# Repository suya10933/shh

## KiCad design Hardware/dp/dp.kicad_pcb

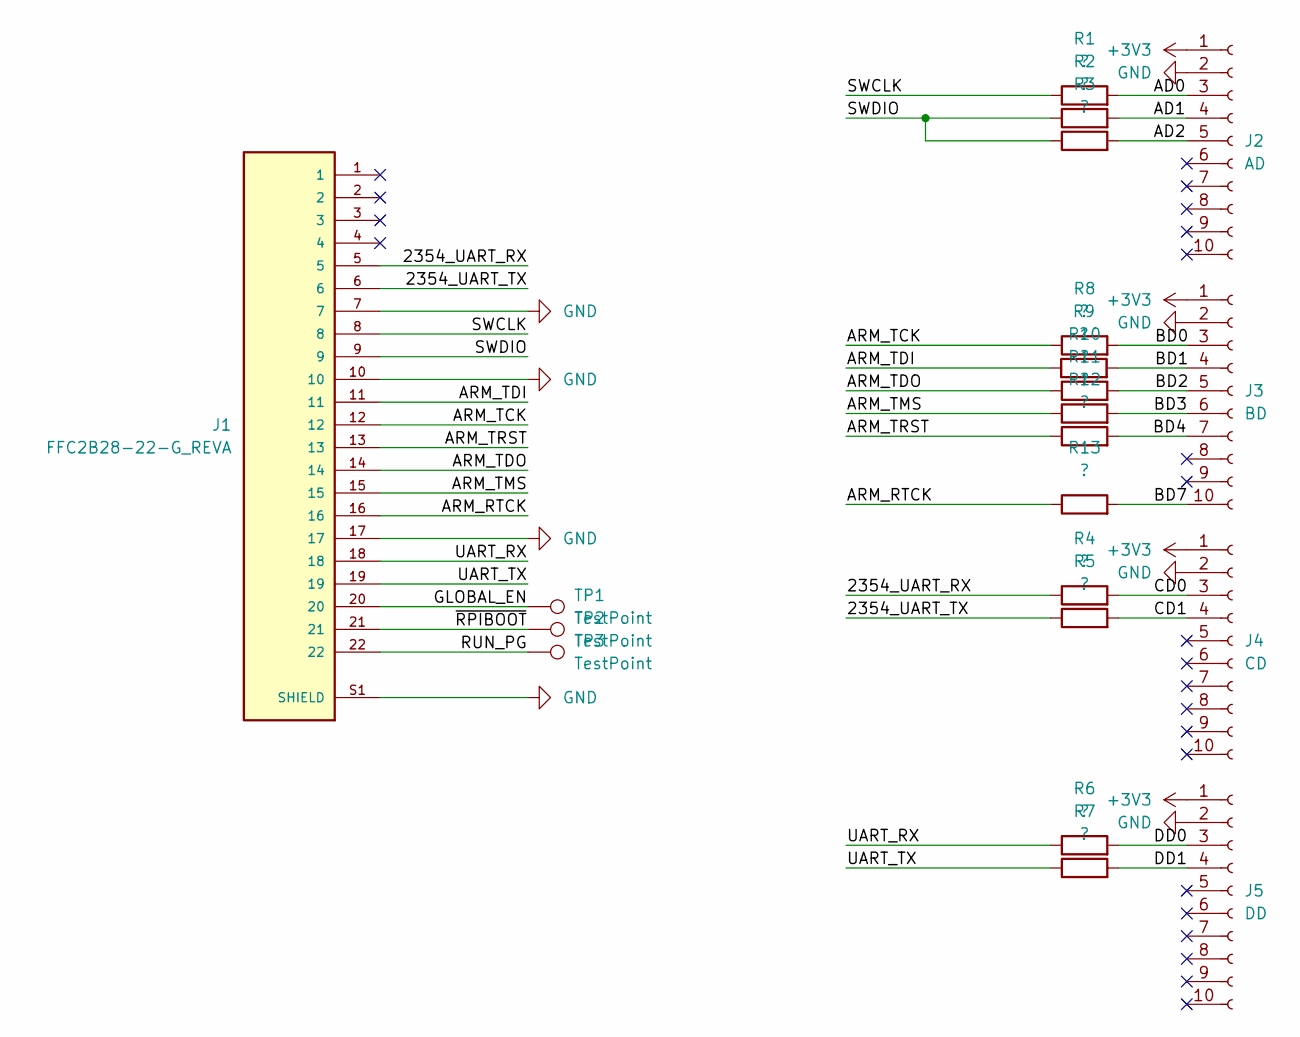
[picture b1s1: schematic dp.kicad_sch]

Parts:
J1: FFC2B28-22-G_REVA; GCT_FFC2B28-22-G_REVA; PARTREV A
J2: AD; PinSocket_1x10_P2.54mm_Vertical
J3: BD; PinSocket_1x10_P2.54mm_Vertical
J4: CD; PinSocket_1x10_P2.54mm_Vertical
J5: DD; PinSocket_1x10_P2.54mm_Vertical
R1, R2, R3, R4, R5, R6, R7, R8, R9, R10, R11, R12, R13: ?; R_0805_2012Metric_Pad1.20x1.40mm_HandSolder
TP1, TP2, TP3: TestPoint; TestPoint_Pad_1.0x1.0mm

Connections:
+3V3: J2.1, J3.1, J4.1, J5.1
/2354_UART_RX: J1.5, R4.1
/2354_UART_TX: J1.6, R5.1
/AD0: J2.3, R1.2
/AD1: J2.4, R2.2
/AD2: J2.5, R3.2
/ARM_RTCK: J1.16, R13.1
/ARM_TCK: J1.12, R8.1
/ARM_TDI: J1.11, R9.1
/ARM_TDO: J1.14, R10.1
/ARM_TMS: J1.15, R11.1
/ARM_TRST: J1.13, R12.1
/BD0: J3.3, R8.2
/BD1: J3.4, R9.2
/BD2: J3.5, R10.2
/BD3: J3.6, R11.2
/BD4: J3.7, R12.2
/BD7: J3.10, R13.2
/CD0: J4.3, R4.2
/CD1: J4.4, R5.2
/DD0: J5.3, R6.2
/DD1: J5.4, R7.2
/GLOBAL_EN: J1.20, TP1.1 (1_1)
/RUN_PG: J1.22, TP3.1 (1_1)
/SWCLK: J1.8, R1.1
/SWDIO: J1.9, R2.1, R3.1
/UART_RX: J1.18, R6.1
/UART_TX: J1.19, R7.1
/~RPIBOOT: J1.21, TP2.1 (1_1)
GND: J1.7, J1.10, J1.17, J1.S1 (SHIELD), J1.S2 (SHIELD), J2.2, J3.2, J4.2, J5.2

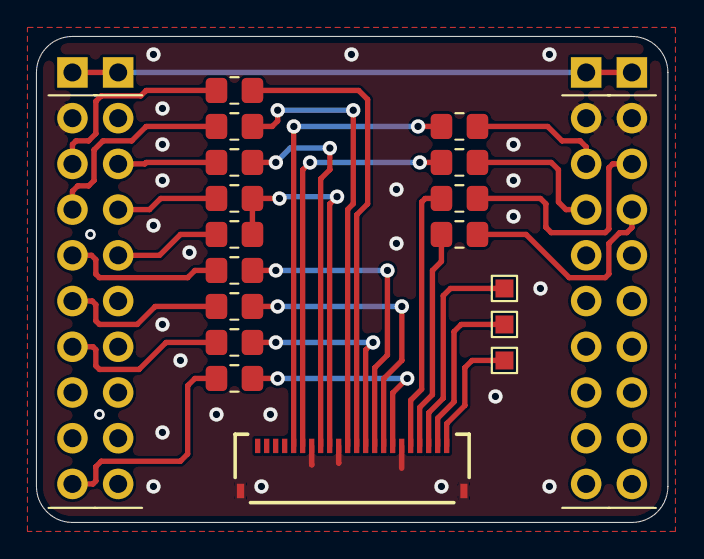
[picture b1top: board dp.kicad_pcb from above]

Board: 2 copper layers, 35.1 x 27.0 mm, 21 parts (0 on the bottom side), 30 nets.

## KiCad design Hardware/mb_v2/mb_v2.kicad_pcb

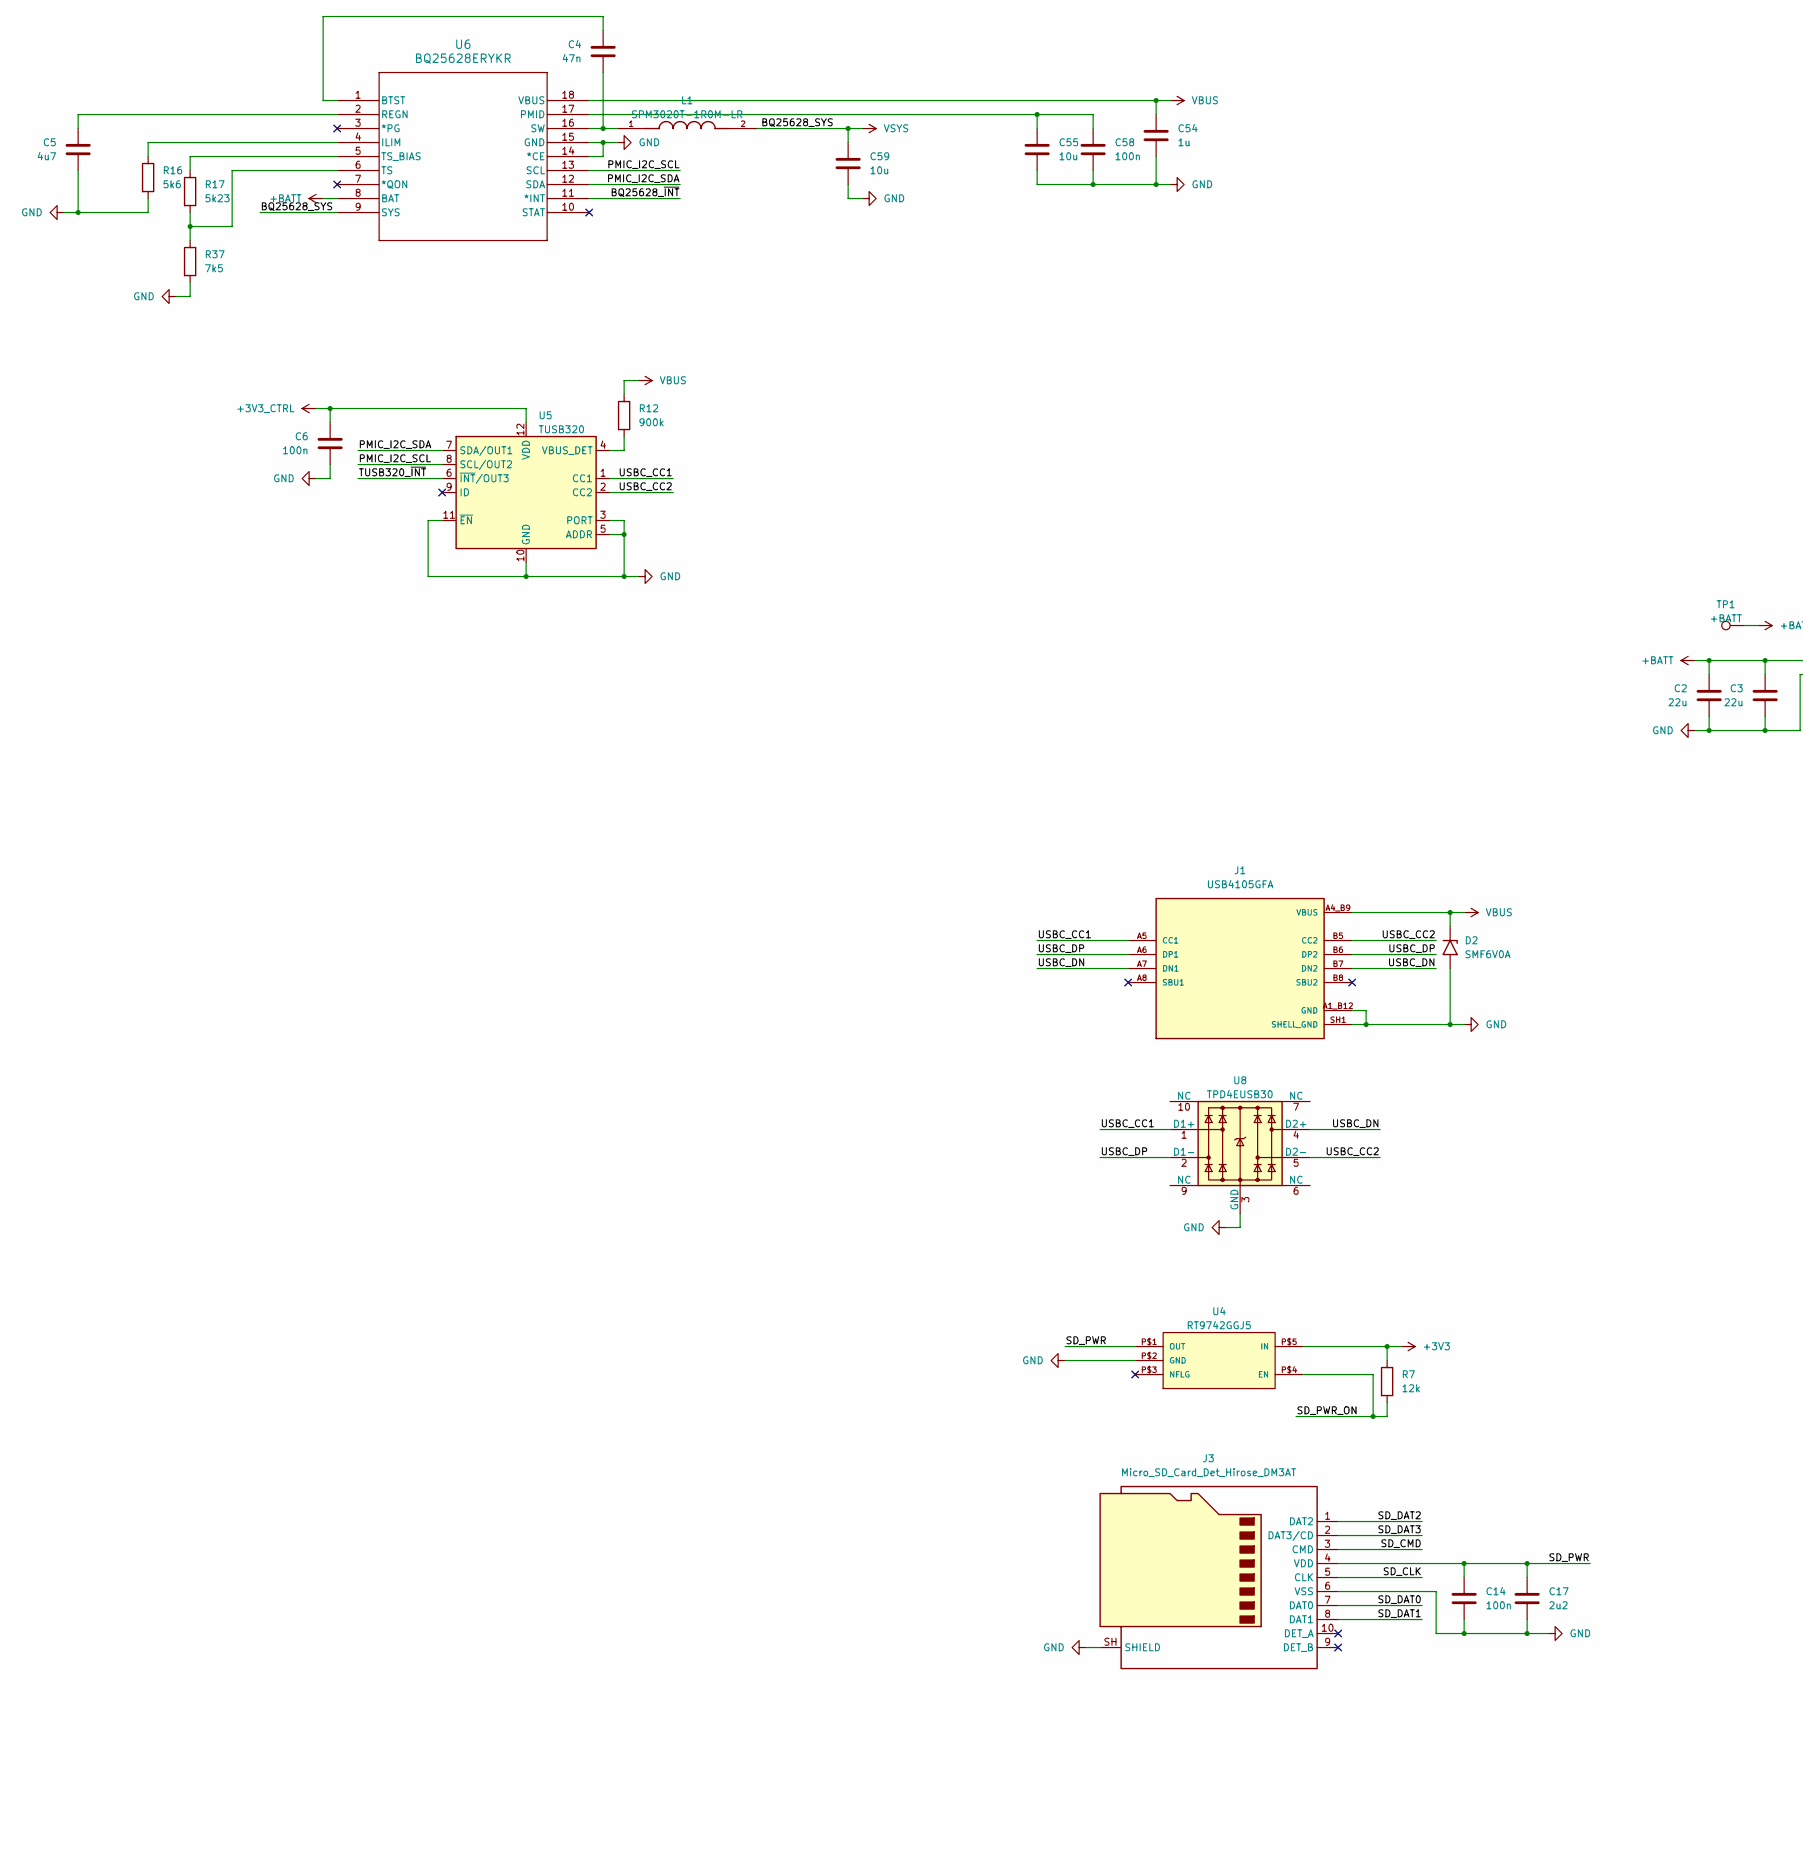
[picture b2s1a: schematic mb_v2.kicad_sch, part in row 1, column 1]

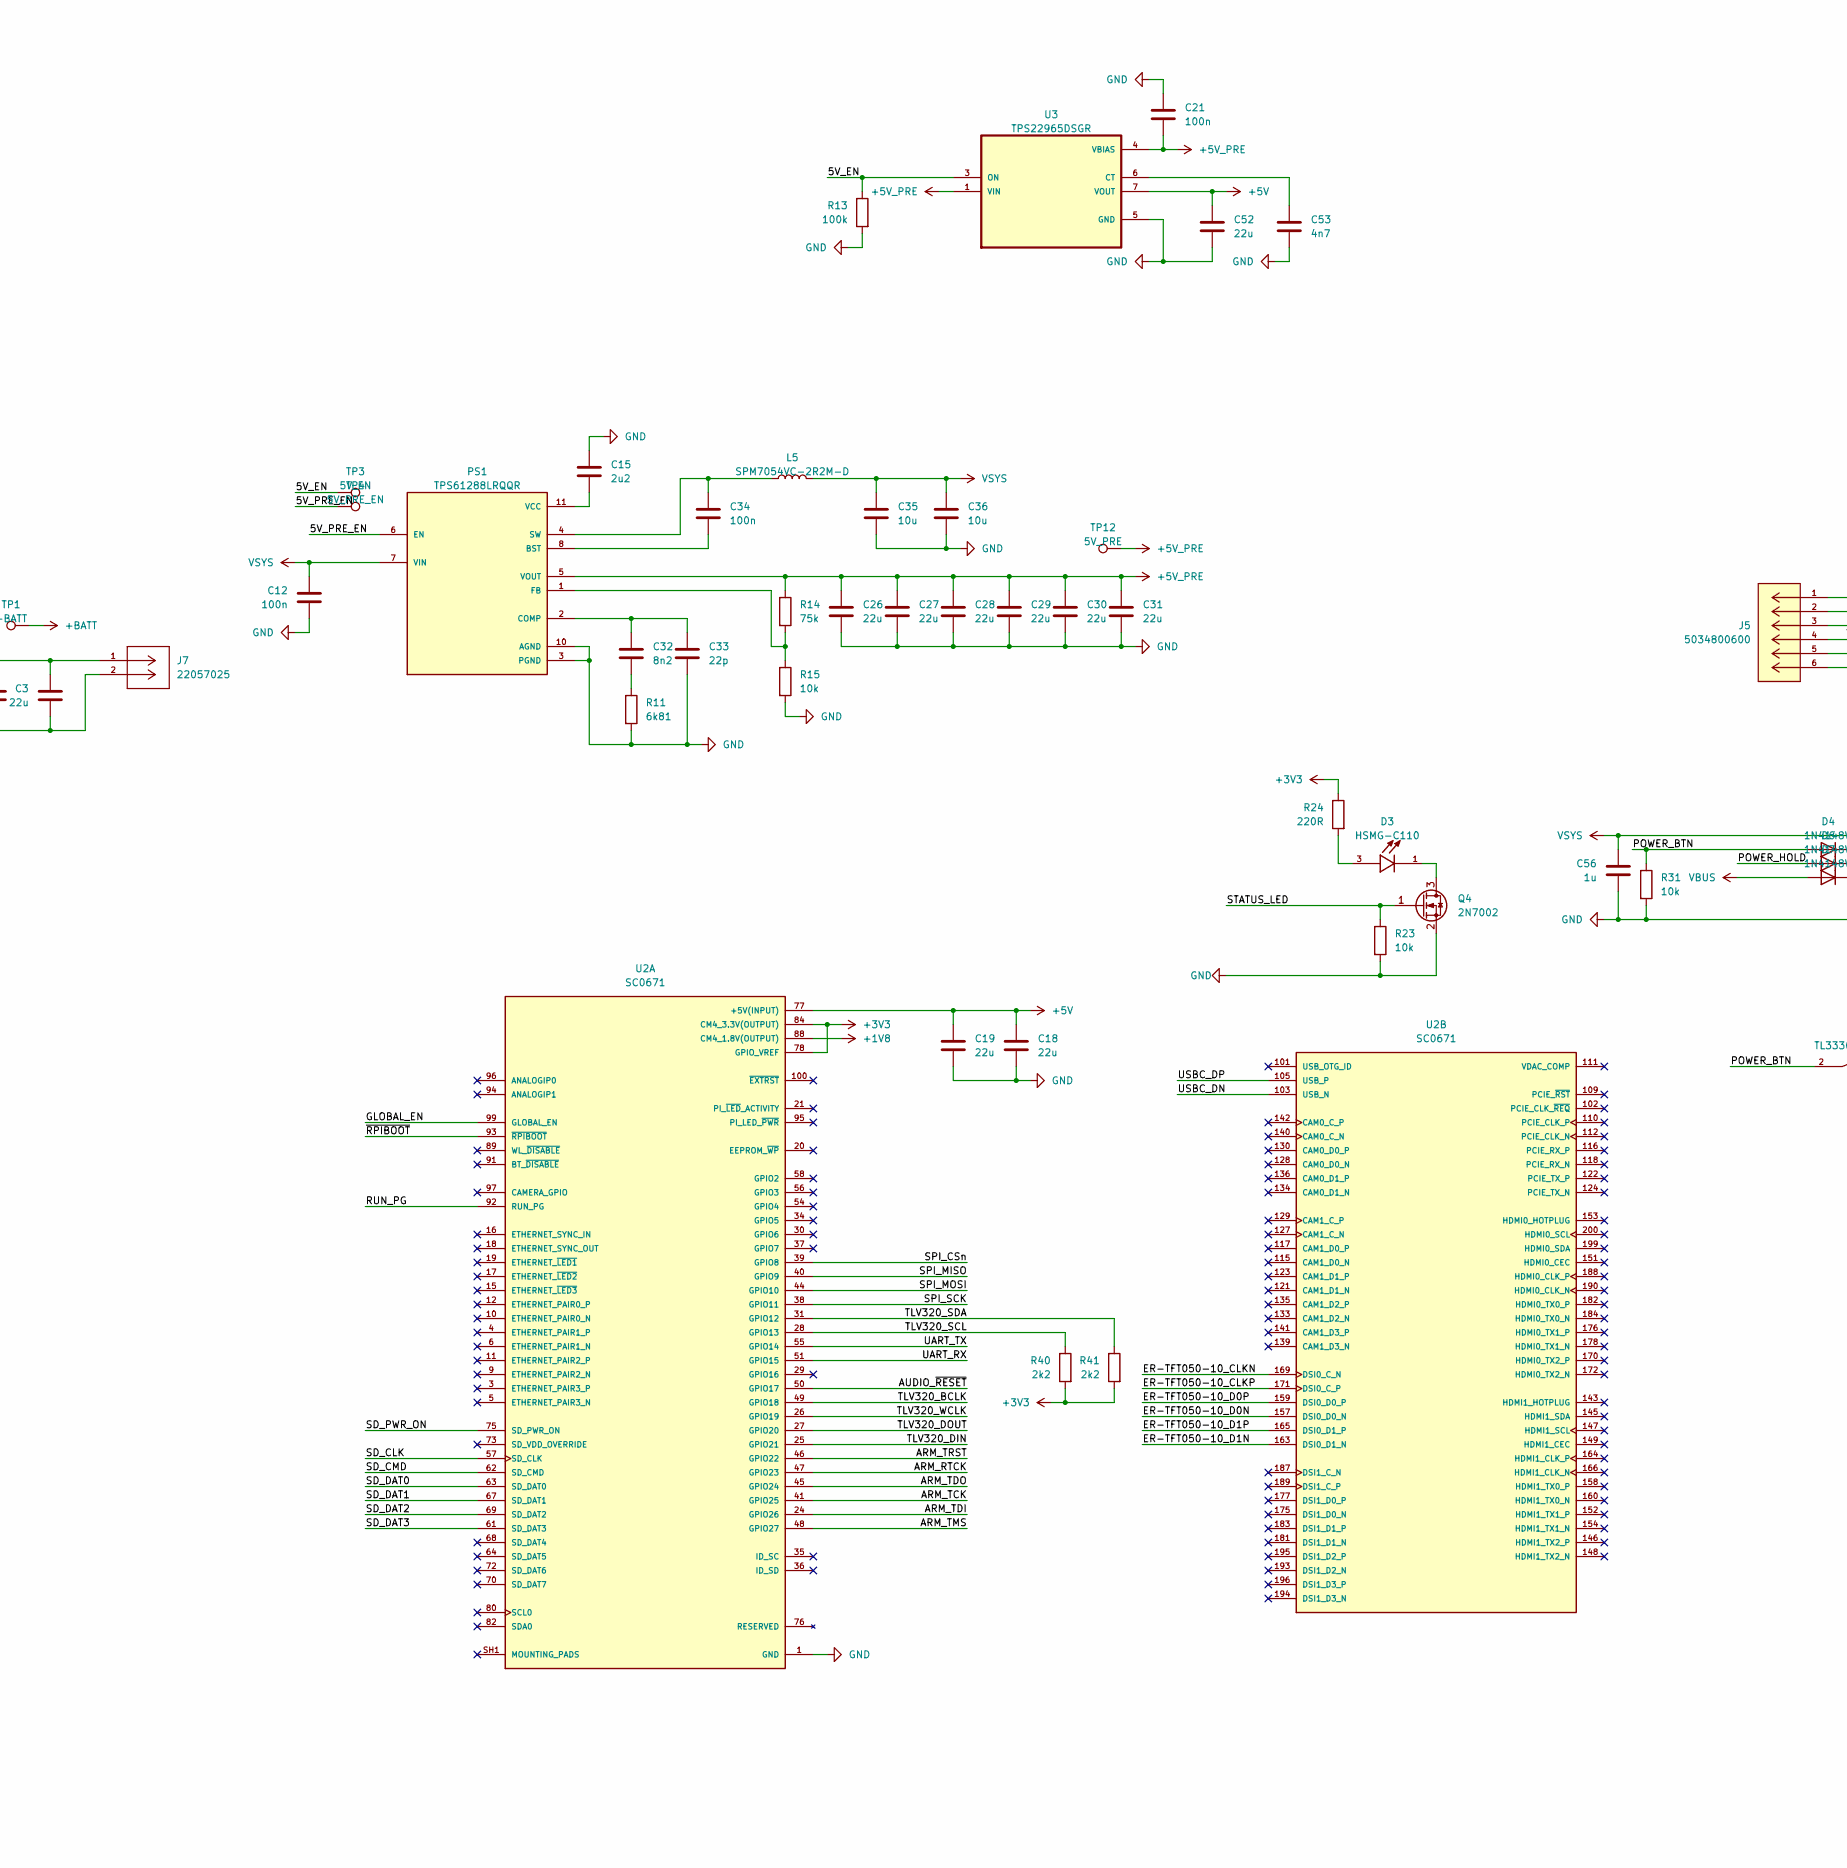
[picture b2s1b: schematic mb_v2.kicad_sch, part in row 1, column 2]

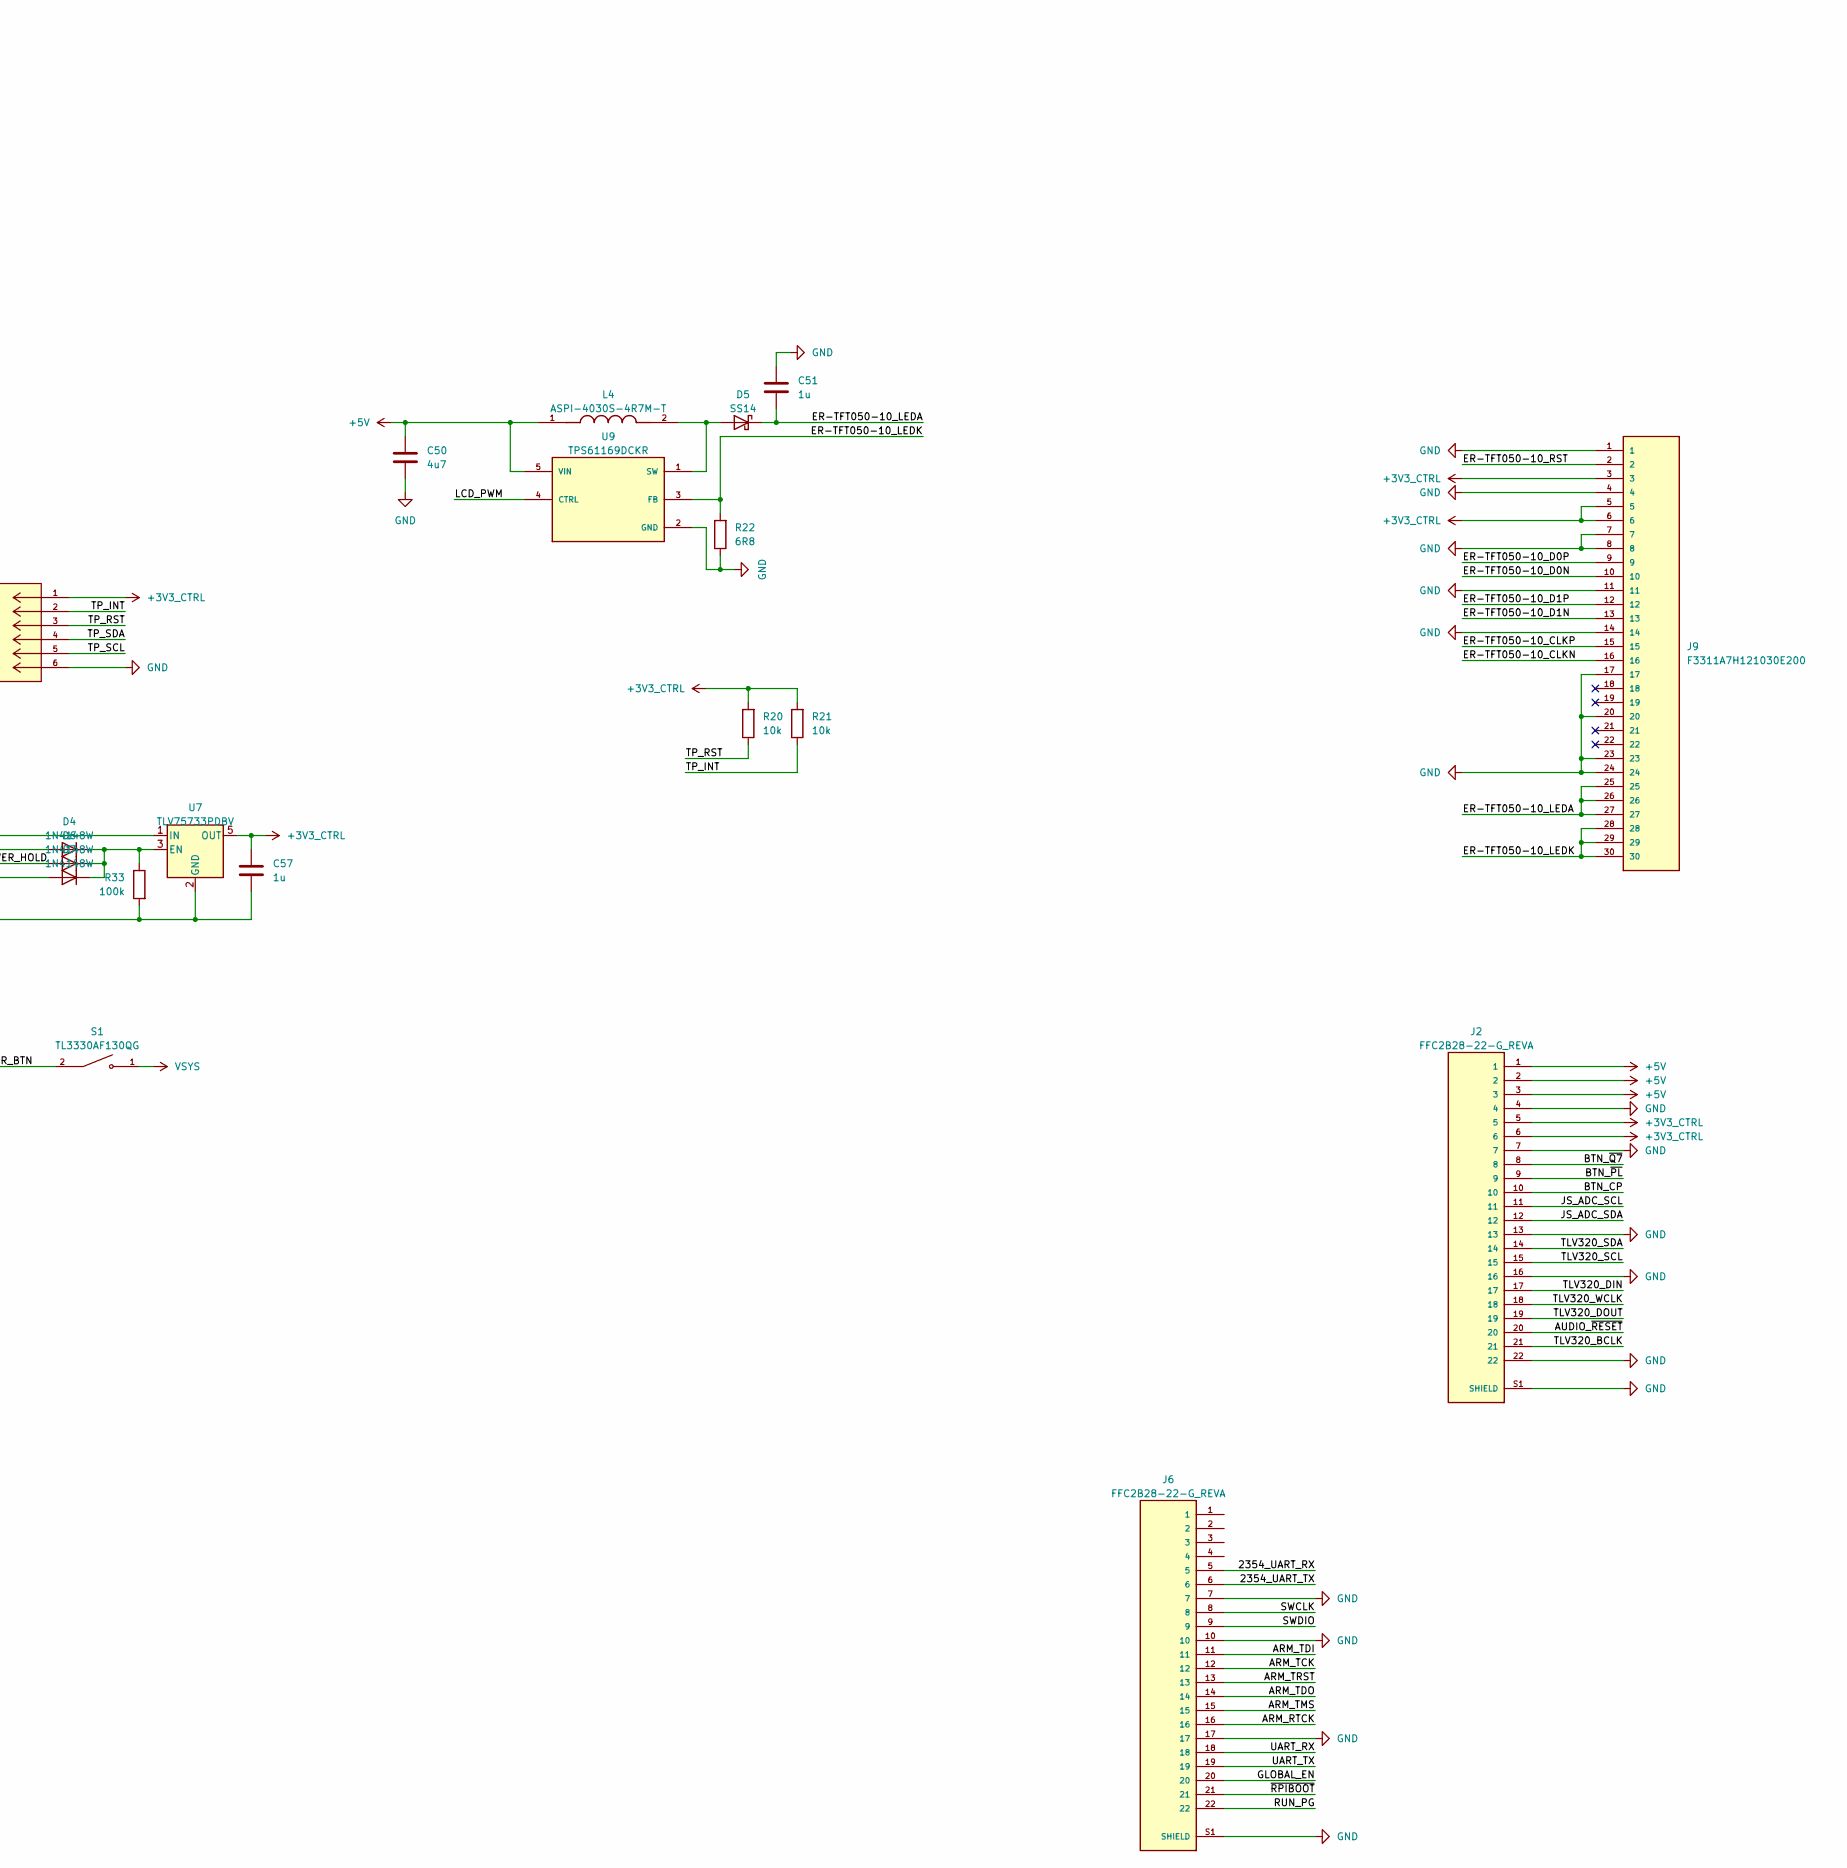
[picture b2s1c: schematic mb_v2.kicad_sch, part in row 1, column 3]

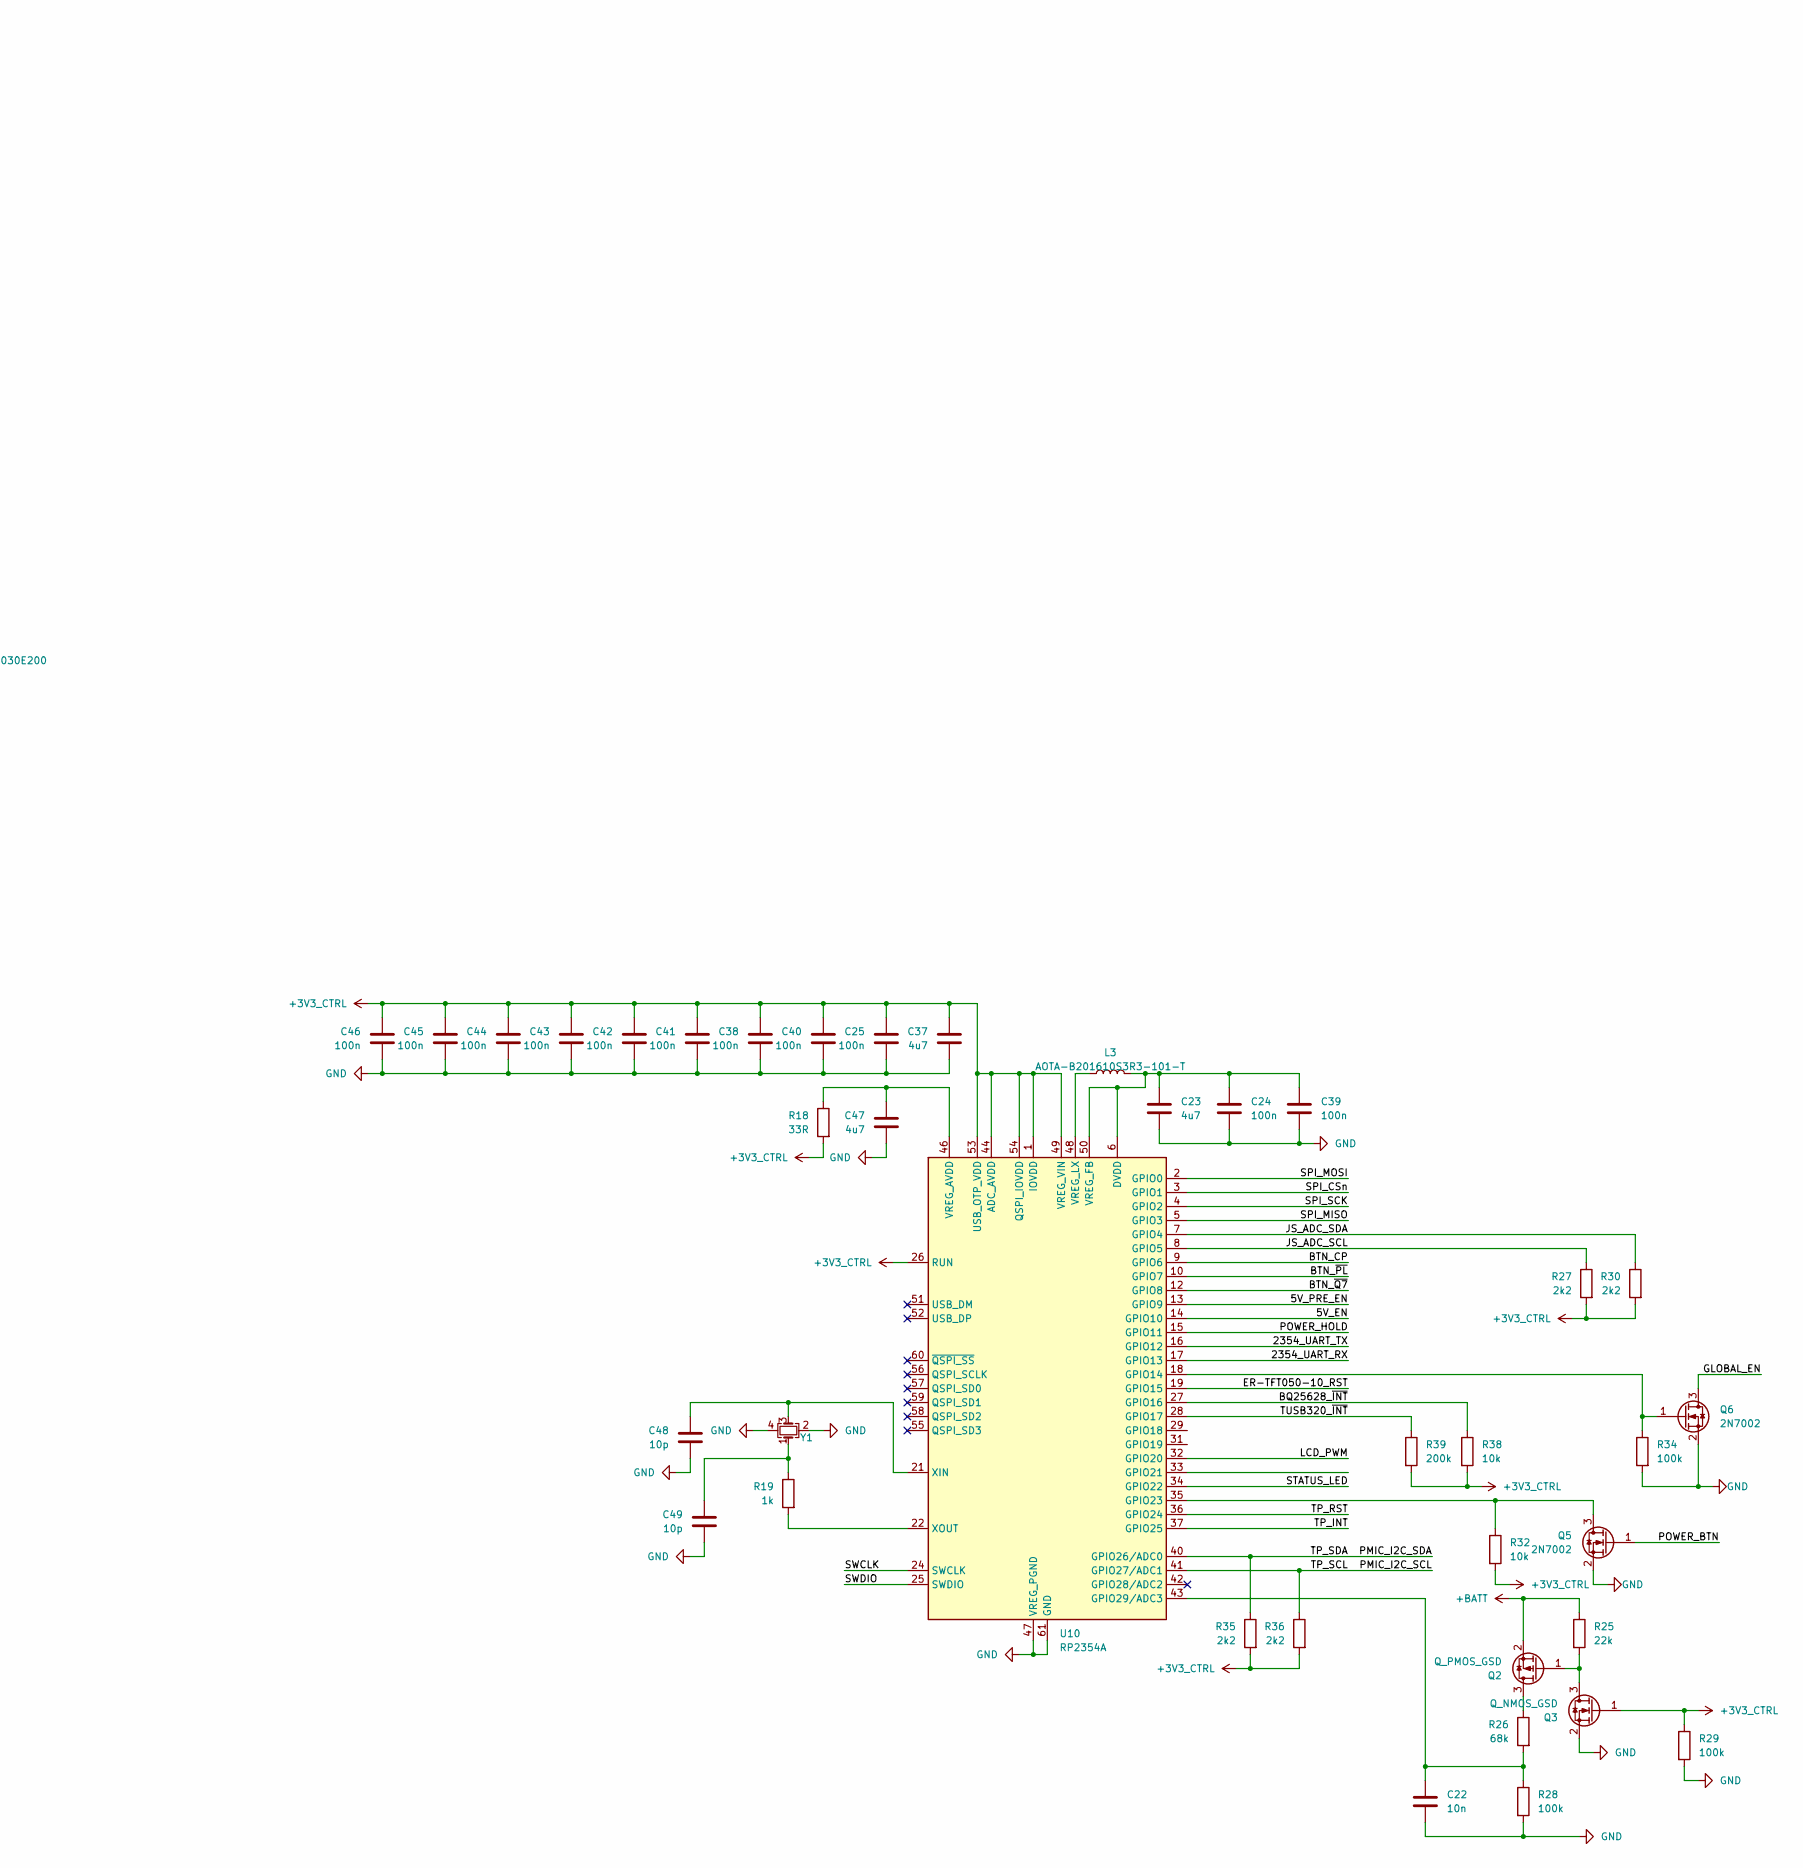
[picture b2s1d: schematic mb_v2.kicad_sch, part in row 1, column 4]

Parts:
C2, C3, C18, C19, C26, C27, C28, C29, C30, C31, C52: 22u; C_0805_2012Metric
C4: 47n; C_0805_2012Metric
C5, C23, C37, C47, C50: 4u7; C_0805_2012Metric
C6, C58: 100n; C_0805_2012Metric
C12, C14, C21, C24, C25, C34, C38, C39, C40, C41, C42, C43, C44, C45, C46: 100n; C_0603_1608Metric
C15, C17: 2u2; C_0805_2012Metric
C22: 10n; C_0603_1608Metric
C32: 8n2; C_0603_1608Metric
C33: 22p; C_0603_1608Metric
C35, C36, C55, C59: 10u; C_0805_2012Metric
C48, C49: 10p; C_0603_1608Metric
C51, C54, C56, C57: 1u; C_0805_2012Metric
C53: 4n7; C_0603_1608Metric
D2: SMF6V0A; D_SMF
D3: HSMG-C110; LED_HSMG-C110; PARTREV March 25, 2022
D4, D6, D7: 1N4148W; D_SOD-123
D5: SS14; D_SMA
J1: USB4105GFA; GCT_USB4105GFA; PARTREV B3
J2, J6: FFC2B28-22-G_REVA; GCT_FFC2B28-22-G_REVA; PARTREV A
J3: Micro_SD_Card_Det_Hirose_DM3AT; microSD_HC_Hirose_DM3AT-SF-PEJM5
J5: 5034800600; 503480-0600_MOL; MANUFACTURER_PART_NUMBER 5034800600
J7: 22057025; CONN_22057025_MOL; MANUFACTURER_PART_NUMBER 22057025
J9: F3311A7H121030E200; AMPHENOL_F3311A7H121030E200; PARTREV A
L1: SPM3020T-1R0M-LR; IND_SPM3020T-1R0M-LR; PARTREV N/A
L3: AOTA-B201610S3R3-101-T; L_Changjiang_FTC201610D; MPN AOTA-B201610S3R3-101-T
L4: ASPI-4030S-4R7M-T; IND_ASPI-4030S-4R7M-T; PARTREV 03.09.13
L5: SPM7054VC-2R2M-D; L_Panasonic_PCC-M0754M
PS1: TPS61288LRQQR; CONV_TPS61288LRQQR; PARTREV C
Q2: Q_PMOS_GSD; SOT-23
Q3: Q_NMOS_GSD; SOT-23
Q4, Q5, Q6: 2N7002; SOT-23
R7: 12k; R_0603_1608Metric
R11: 6k81; R_0603_1608Metric
R12: 900k; R_0603_1608Metric
R13, R28, R29, R33, R34: 100k; R_0603_1608Metric
R14: 75k; R_0603_1608Metric
R15, R20, R21, R23, R31, R32, R38: 10k; R_0603_1608Metric
R16: 5k6; R_0603_1608Metric
R17: 5k23; R_0603_1608Metric
R18: 33R; R_0603_1608Metric
R19: 1k; R_0603_1608Metric
R22: 6R8; R_0603_1608Metric
R24: 220R; R_0603_1608Metric
R25: 22k; R_0603_1608Metric
R26: 68k; R_0603_1608Metric
R27, R30, R35, R36, R40, R41: 2k2; R_0603_1608Metric
R37: 7k5; R_0603_1608Metric
R39: 200k; R_0603_1608Metric
S1: TL3330AF130QG; SW_TL3330AF130QG; PARTREV B
TP1: +BATT; TestPoint_Pad_1.0x1.0mm
TP3: 5V_EN; TestPoint_Pad_1.0x1.0mm
TP4: 5V_PRE_EN; TestPoint_Pad_1.0x1.0mm
TP12: 5V_PRE; TestPoint_Pad_1.0x1.0mm
U2: SC0671; MODULE_SC0671; PARTREV 2021-10-12
U3: TPS22965DSGR; SON50P200X200X80-9N
U4: RT9742GGJ5; TSOT-23-5
U5: TUSB320; Texas_X2QFN-12_1.6x1.6mm_P0.4mm
U6: BQ25628ERYKR; WQFN-HR18__RYK_TEX
U7: TLV75733PDBV; SOT-23-5
U8: TPD4EUSB30; USON-10_2.5x1.0mm_P0.5mm
U9: TPS61169DCKR; SOT65P210X110-5N; PARTREV A; DigiKey_Part_Number 296-40821-1-ND
U10: RP2354A; QFN-60-1EP_7x7mm_P0.4mm_EP3.4x3.4mm
Y1: Crystal; Crystal_SMD_3225-4Pin_3.2x2.5mm; MPN ABM8-272-T3

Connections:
+1V8: U2.88 (CM4_1.8V(OUTPUT)), U2.90 (CM4_1.8V(OUTPUT))
+3V3: R7.1, R24.1, R40.2, R41.2, U2.78 (GPIO_VREF), U2.84 (CM4_3.3V(OUTPUT)), U2.86 (CM4_3.3V(OUTPUT)), U4.P$5 (IN)
+3V3_CTRL: C6.1, C25.1, C37.1, C38.1, C40.1, C41.1, C42.1, C43.1, C44.1, C45.1, C46.1, C57.1, J2.5, J2.6, J5.1, J9.3, J9.5, J9.6, Q3.1 (G), R18.2, R20.2, R21.2, R27.2, R29.1, R30.2, R32.2, R35.2, R36.2, R38.2, R39.2, U5.12 (VDD), U7.5 (OUT), U10.1 (IOVDD), U10.11 (IOVDD), U10.20 (IOVDD), U10.26 (RUN), U10.30 (IOVDD), U10.38 (IOVDD), U10.44 (ADC_AVDD), U10.45 (IOVDD), U10.49 (VREG_VIN), U10.53 (USB_OTP_VDD), U10.54 (QSPI_IOVDD)
+5V: C18.1, C19.1, C50.1, C52.1, J2.1, J2.2, J2.3, L4.1, U2.77 (+5V(INPUT)), U2.79 (+5V(INPUT)), U2.81 (+5V(INPUT)), U2.83 (+5V(INPUT)), U2.85 (+5V(INPUT)), U2.87 (+5V(INPUT)), U3.7 (VOUT), U3.8 (VOUT), U9.5 (VIN)
+5V_PRE: C21.2, C26.1, C27.1, C28.1, C29.1, C30.1, C31.1, PS1.5 (VOUT), R14.1, TP12.1 (1_1), U3.1 (VIN), U3.2 (VIN), U3.4 (VBIAS)
+BATT: C2.1, C3.1, J7.1, Q2.2 (S), R25.1, TP1.1 (1_1), U6.8 (BAT)
/5V_EN: R13.1, TP3.1 (1_1), U3.3 (ON), U10.14 (GPIO10)
/5V_PRE_EN: PS1.6 (EN), TP4.1 (1_1), U10.13 (GPIO9)
/2354_UART_RX: J6.5, U10.17 (GPIO13)
/2354_UART_TX: J6.6, U10.16 (GPIO12)
/ARM_RTCK: J6.16, U2.47 (GPIO23)
/ARM_TCK: J6.12, U2.41 (GPIO25)
/ARM_TDI: J6.11, U2.24 (GPIO26)
/ARM_TDO: J6.14, U2.45 (GPIO24)
/ARM_TMS: J6.15, U2.48 (GPIO27)
/ARM_TRST: J6.13, U2.46 (GPIO22)
/AUDIO_~RESET: J2.20, U2.50 (GPIO17)
/BQ25628_~INT: R38.1, U6.11 (*INT), U10.27 (GPIO16)
/BTN_CP: J2.10, U10.9 (GPIO6)
/BTN_~PL: J2.9, U10.10 (GPIO7)
/BTN_~Q7: J2.8, U10.12 (GPIO8)
/ER-TFT050-10_CLKN: J9.16, U2.169 (DSI0_C_N)
/ER-TFT050-10_CLKP: J9.15, U2.171 (DSI0_C_P)
/ER-TFT050-10_D0N: J9.10, U2.157 (DSI0_D0_N)
/ER-TFT050-10_D0P: J9.9, U2.159 (DSI0_D0_P)
/ER-TFT050-10_D1N: J9.13, U2.163 (DSI0_D1_N)
/ER-TFT050-10_D1P: J9.12, U2.165 (DSI0_D1_P)
/ER-TFT050-10_LEDA: C51.2, D5.1 (K), J9.25, J9.26, J9.27
/ER-TFT050-10_LEDK: J9.28, J9.29, J9.30, R22.2, U9.3 (FB)
/ER-TFT050-10_RST: J9.2, U10.19 (GPIO15)
/GLOBAL_EN: J6.20, Q6.3 (D), U2.99 (GLOBAL_EN)
/JS_ADC_SCL: J2.11, R27.1, U10.8 (GPIO5)
/JS_ADC_SDA: J2.12, R30.1, U10.7 (GPIO4)
/LCD_PWM: U9.4 (CTRL), U10.32 (GPIO20)
/PMIC_I2C_SCL: J5.5, R36.1, U5.8 (SCL/OUT2), U6.13 (SCL), U10.41 (GPIO27/ADC1)
/PMIC_I2C_SDA: J5.4, R35.1, U5.7 (SDA/OUT1), U6.12 (SDA), U10.40 (GPIO26/ADC0)
/POWER_BTN: D4.2 (A), Q5.1 (G), R31.1, S1.2
/POWER_HOLD: D6.2 (A), U10.15 (GPIO11)
/RUN_PG: J6.22, U2.92 (RUN_PG)
/SD_CLK: J3.5 (CLK), U2.57 (SD_CLK)
/SD_CMD: J3.3 (CMD), U2.62 (SD_CMD)
/SD_DAT0: J3.7 (DAT0), U2.63 (SD_DAT0)
/SD_DAT1: J3.8 (DAT1), U2.67 (SD_DAT1)
/SD_DAT2: J3.1 (DAT2), U2.69 (SD_DAT2)
/SD_DAT3: J3.2 (DAT3/CD), U2.61 (SD_DAT3)
/SD_PWR: C14.1, C17.1, J3.4 (VDD), U4.P$1 (OUT)
/SD_PWR_ON: R7.2, U2.75 (SD_PWR_ON), U4.P$4 (EN)
/SPI_CSn: U2.39 (GPIO8), U10.3 (GPIO1)
/SPI_MISO: U2.40 (GPIO9), U10.5 (GPIO3)
/SPI_MOSI: U2.44 (GPIO10), U10.2 (GPIO0)
/SPI_SCK: U2.38 (GPIO11), U10.4 (GPIO2)
/STATUS_LED: Q4.1 (G), R23.1, U10.34 (GPIO22)
/SWCLK: J6.8, U10.24 (SWCLK)
/SWDIO: J6.9, U10.25 (SWDIO)
/TLV320_BCLK: J2.21, U2.49 (GPIO18)
/TLV320_DIN: J2.17, U2.25 (GPIO21)
/TLV320_DOUT: J2.19, U2.27 (GPIO20)
/TLV320_SCL: J2.15, R40.1, U2.28 (GPIO13)
/TLV320_SDA: J2.14, R41.1, U2.31 (GPIO12)
/TLV320_WCLK: J2.18, U2.26 (GPIO19)
/TP_INT: J5.2, R21.1, U10.37 (GPIO25)
/TP_RST: J5.3, R20.1, U10.36 (GPIO24)
/TUSB320_~INT: R39.1, U5.6 (~INT/OUT3), U10.28 (GPIO17)
/UART_RX: J6.18, U2.51 (GPIO15)
/UART_TX: J6.19, U2.55 (GPIO14)
/USBC_CC1: J1.A5 (CC1), U5.1 (CC1), U8.1 (D1+)
/USBC_CC2: J1.B5 (CC2), U5.2 (CC2), U8.5 (D2-)
/USBC_DN: J1.A7 (DN1), J1.B7 (DN2), U2.103 (USB_N), U8.4 (D2+)
/USBC_DP: J1.A6 (DP1), J1.B6 (DP2), U2.105 (USB_P), U8.2 (D1-)
/~RPIBOOT: J6.21, U2.93 (~RPIBOOT)
GND: C2.2, C3.2, C5.2, C6.2, C12.2, C14.2, C15.1, C17.2, C18.2, C19.2, C21.1, C22.2, C23.2, C24.2, C25.2, C26.2, C27.2, C28.2, C29.2, C30.2, C31.2, C33.2, C35.2, C36.2, C37.2, C38.2, C39.2, C40.2, C41.2, C42.2, C43.2, C44.2, C45.2, C46.2, C47.2, C48.2, C49.2, C50.2, C51.1, C52.2, C53.2, C54.2, C55.2, C56.2, C57.2, C58.2, C59.2, D2.2 (A2), J1.A1_B12 (GND), J1.B1_A12 (GND), J1.SH1 (SHELL_GND), J1.SH2 (SHELL_GND), J1.SH3 (SHELL_GND), J1.SH4 (SHELL_GND), J2.4, J2.7, J2.13, J2.16, J2.22, J2.S1 (SHIELD), J2.S2 (SHIELD), J3.6 (VSS), J3.SH (SHIELD), J5.6, J6.7, J6.10, J6.17, J6.S1 (SHIELD), J6.S2 (SHIELD), J7.2, J9.1, J9.4, J9.7, J9.8, J9.11, J9.14, J9.17, J9.20, J9.23, J9.24, PS1.3 (PGND), PS1.10 (AGND), Q3.2 (S), Q4.2 (S), Q5.2 (S), Q6.2 (S), R11.2, R13.2, R15.2, R16.2, R22.1, R23.2, R28.2, R29.2, R31.2, R33.2, R34.2, R37.2, U2.1 (GND), U2.2 (GND), U2.7 (GND), U2.8 (GND), U2.13 (GND), U2.14 (GND), U2.22 (GND), U2.23 (GND), U2.32 (GND), U2.33 (GND), U2.42 (GND), U2.43 (GND), U2.52 (GND), U2.53 (GND), U2.59 (GND), U2.60 (GND), U2.65 (GND), U2.66 (GND), U2.71 (GND), U2.74 (GND), U2.98 (GND), U2.107 (GND), U2.108 (GND), U2.113 (GND), U2.114 (GND), U2.119 (GND), U2.120 (GND), U2.125 (GND), U2.126 (GND), U2.131 (GND), U2.132 (GND), U2.137 (GND), U2.138 (GND), U2.144 (GND), U2.150 (GND), U2.155 (GND), U2.156 (GND), U2.161 (GND), U2.162 (GND), U2.167 (GND), U2.168 (GND), U2.173 (GND), U2.174 (GND), U2.179 (GND), U2.180 (GND), U2.185 (GND), U2.186 (GND), U2.191 (GND), U2.192 (GND), U2.197 (GND), U2.198 (GND), U3.5 (GND), U3.9 (GND), U3.9_1 (GND), U3.9_2 (GND), U4.P$2 (GND), U5.3 (PORT), U5.5 (ADDR), U5.10 (GND), U5.11 (~EN), U6.14 (*CE), U6.15 (GND), U7.2 (GND), U8.3 (GND), U8.8 (GND), U9.2 (GND), U10.47 (VREG_PGND), U10.61 (GND), Y1.2, Y1.4
unnamed: C32.2, R11.1
unnamed: C34.1, L5.1, PS1.4 (SW), PS1.9 (SW)
unnamed: C49.1, R19.1, Y1.1
unnamed: D3.3, R24.2
unnamed: D4.1 (K), D6.1 (K), D7.1 (K), R33.1, U7.3 (EN)
unnamed: D5.2 (A), L4.2, U9.1 (SW)
unnamed: C34.2, PS1.8 (BST)
unnamed: C32.1, C33.1, PS1.2 (COMP)
unnamed: PS1.1 (FB), R14.2, R15.1
unnamed: C15.2, PS1.11 (VCC)
unnamed: Q2.3 (D), R26.1
unnamed: Q2.1 (G), Q3.3 (D), R25.2
unnamed: D3.1, Q4.3 (D)
unnamed: Q5.3 (D), R32.1, U10.35 (GPIO23)
unnamed: Q6.1 (G), R34.1, U10.18 (GPIO14)
unnamed: C53.1, U3.6 (CT)
unnamed: R12.2, U5.4 (VBUS_DET)
unnamed: C4.1, U6.1 (BTST)
unnamed: R16.1, U6.4 (ILIM)
unnamed: C55.1, C58.1, U6.17 (PMID)
unnamed: C5.1, U6.2 (REGN)
unnamed: C4.2, L1.1, U6.16 (SW)
unnamed: R17.2, R37.1, U6.6 (TS)
unnamed: R17.1, U6.5 (TS_BIAS)
unnamed: C22.1, R26.2, R28.1, U10.43 (GPIO29/ADC3)
unnamed: C47.1, R18.1, U10.46 (VREG_AVDD)
unnamed: C23.1, C24.1, C39.1, L3.2, U10.6 (DVDD), U10.23 (DVDD), U10.39 (DVDD), U10.50 (VREG_FB)
unnamed: L3.1, U10.48 (VREG_LX)
unnamed: C48.1, U10.21 (XIN), Y1.3
unnamed: R19.2, U10.22 (XOUT)
VBUS: C54.1, D2.1 (A1), D7.2 (A), J1.A4_B9 (VBUS), J1.B4_A9 (VBUS), R12.1, U6.18 (VBUS)
VSYS: C12.1, C35.1, C36.1, C56.1, C59.1, L1.2, L5.2, PS1.7 (VIN), S1.1, U6.9 (SYS), U7.1 (IN)
